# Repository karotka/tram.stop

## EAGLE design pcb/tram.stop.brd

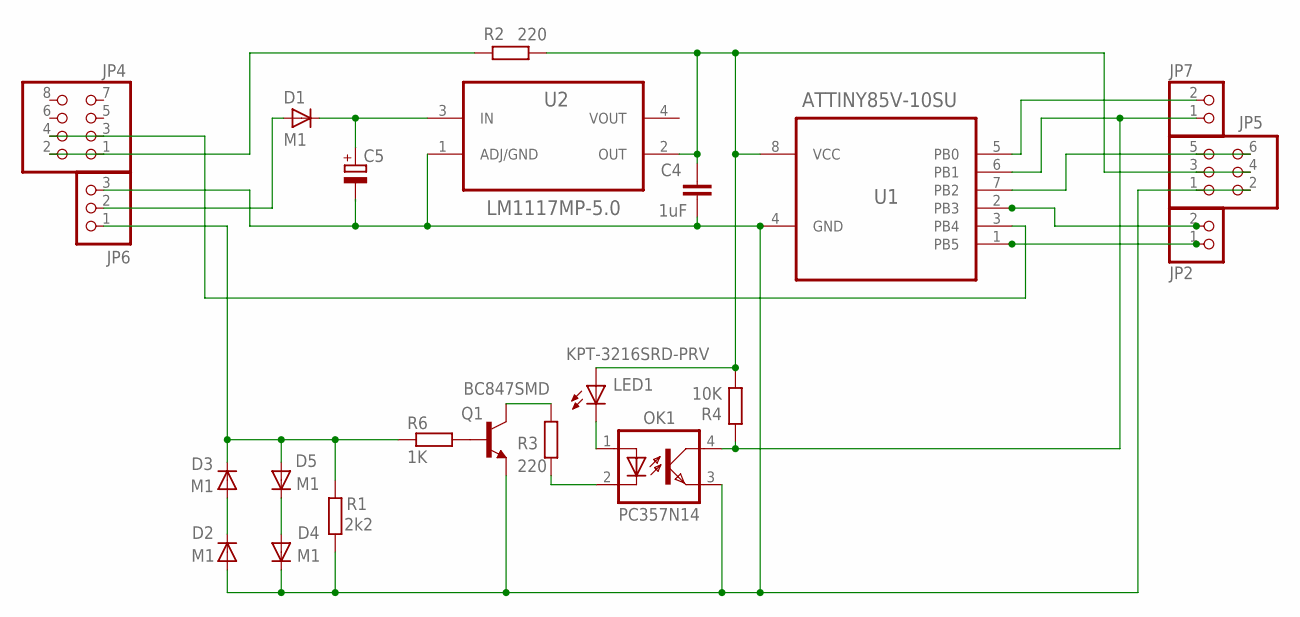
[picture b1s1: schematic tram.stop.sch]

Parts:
C4: 1uF; C0402
C5: CPOL-EUSMCD; SMC_D
D1, D2, D3, D4, D5: M1; SMB
JP2, JP7: PINHD-1X2/90; 1X02/90
JP4: PINHD-2X4/90; 2X04/90
JP5: PINHD-2X3/90; 2X03/90
JP6: PINHD-1X3/90; 1X03/90
LED1: KPT-3216SRD-PRV; SML1206
OK1: PC357N14; SMD4
Q1: BC847SMD; SOT23
R1: 2k2; R1206
R2, R3: 220; R1206
R4: 10K; R1206
R6: 1K; R1206
U1: ATTINY85V-10SU; SOIC127P798X216-8N
U2: LM1117MP-5.0; SOT230P696X180-4N

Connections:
220: LED1.C, OK1.1 (A)
JP1: D3.C, D5.A, JP6.1, R1.1, R6.1
JP2: C4.2, D2.A, D4.C, JP5.1, JP5.2, JP6.3, OK1.3 (EMIT), Q1.2 (E), R1.2, U1.4 (GND), U2.1 (ADJ/GND)
unnamed: JP2.1, U1.1 (PB5)
unnamed: JP2.2, U1.2 (PB3)
unnamed: D2.C, D3.A
unnamed: D4.A, D5.C
unnamed: Q1.1 (B), R6.2
unnamed: Q1.3 (C), R3.1
unnamed: OK1.2 (C), R3.2
unnamed: JP5.5, JP5.6, U1.7 (PB2)
unnamed: JP7.2, U1.5 (PB0)
unnamed: JP4.1, JP4.2, R2.1
unnamed: JP7.1, OK1.4 (COL), R4.1, U1.6 (PB1)
unnamed: C4.1, JP5.3, JP5.4, LED1.A, R2.2, R4.2, U1.8 (VCC), U2.2 (OUT)
unnamed: D1.A, JP6.2
unnamed: C5.+, D1.C, U2.3 (IN)
RED2: JP4.3, JP4.4, U1.3 (PB4)

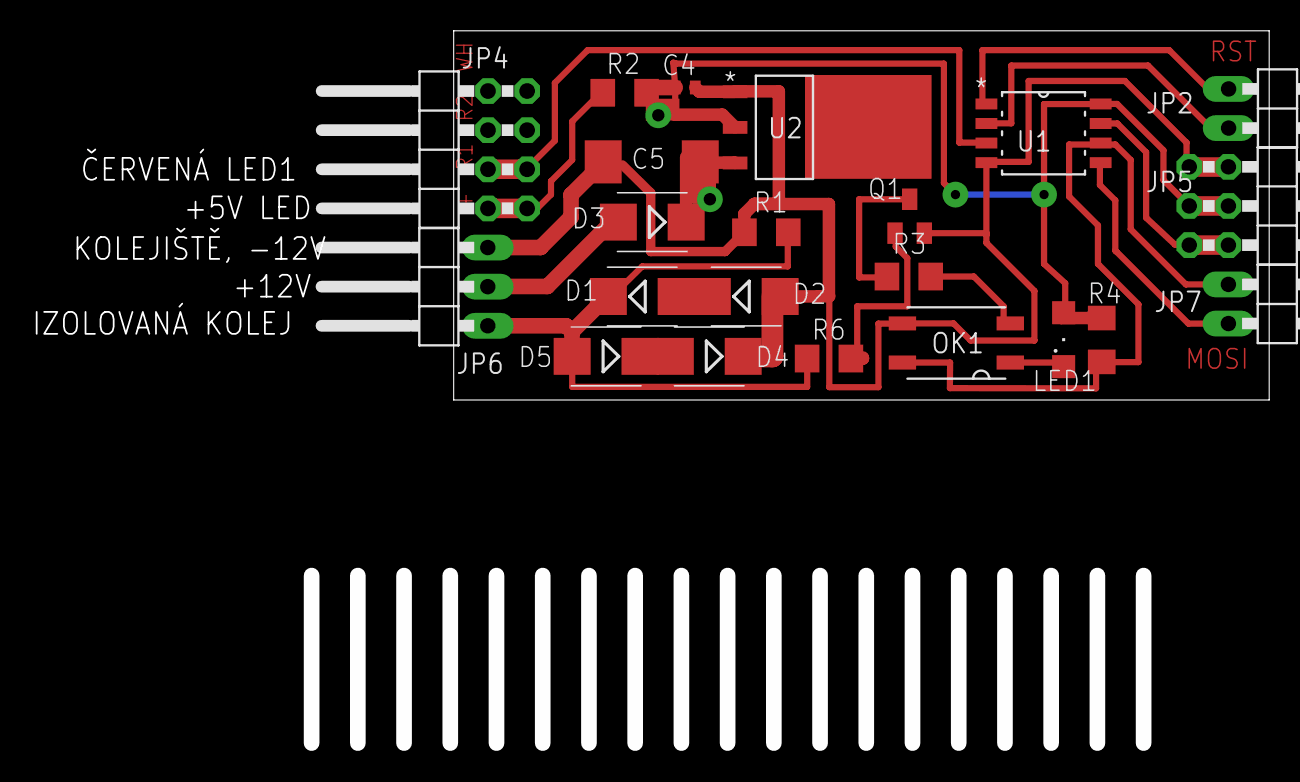
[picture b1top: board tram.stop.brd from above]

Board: 2 copper layers, 79.4 x 45.7 mm, 22 parts (0 on the bottom side), 18 nets.

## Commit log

2013-09-12 #! add files
2013-09-24 #! finalize code
